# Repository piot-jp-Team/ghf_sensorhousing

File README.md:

# ghf_sensorhousing
## 農園センサーユニットハウジング
- arduino pro mini
- MH-Z19B 二酸化炭素センサ または　S-300G 二酸化炭素センサ
- AM2320 温湿度センサー
- リニア照度センサ
- 土壌水分センサ

## 仕組み
iot通信モジュールへRS485で取得データを送ります。  
sakura.io + arduino UNO  
sakura.ioから、laravel製のグラフで表示します。  
https://github.com/piot-jp-Team/ghf_webapp （日々更新中）  

sakura.ioとの接続（Web Socket部分）は、https://github.com/piot-jp-Team/ghf_sakuraIO_wss_client  
今後はsigfox,lorawanも利用したいと思います。

## 使用するライブラリ   
(サーバ側)
- nginx, php7
- websocket クライアント　ratchetphp/Pawl
- phpフレームワーク laravel 5.6
- LaravelCharts
- mysql 5.7

(組み込み側)
- Arduino
- modbus/master slave
- S-300G or mhz19_uart
- Adafruit_Sensor
- Adafruit_AM2320
- sakura.io

## 開発ツール
- 筐体設計 OpenSCAD, FreeCAD
- PCB設計 Eagle6.6
- ファームウエア arduino IDE1.8.5
- エディタはATOM, PlantUML, Netbeans etc.

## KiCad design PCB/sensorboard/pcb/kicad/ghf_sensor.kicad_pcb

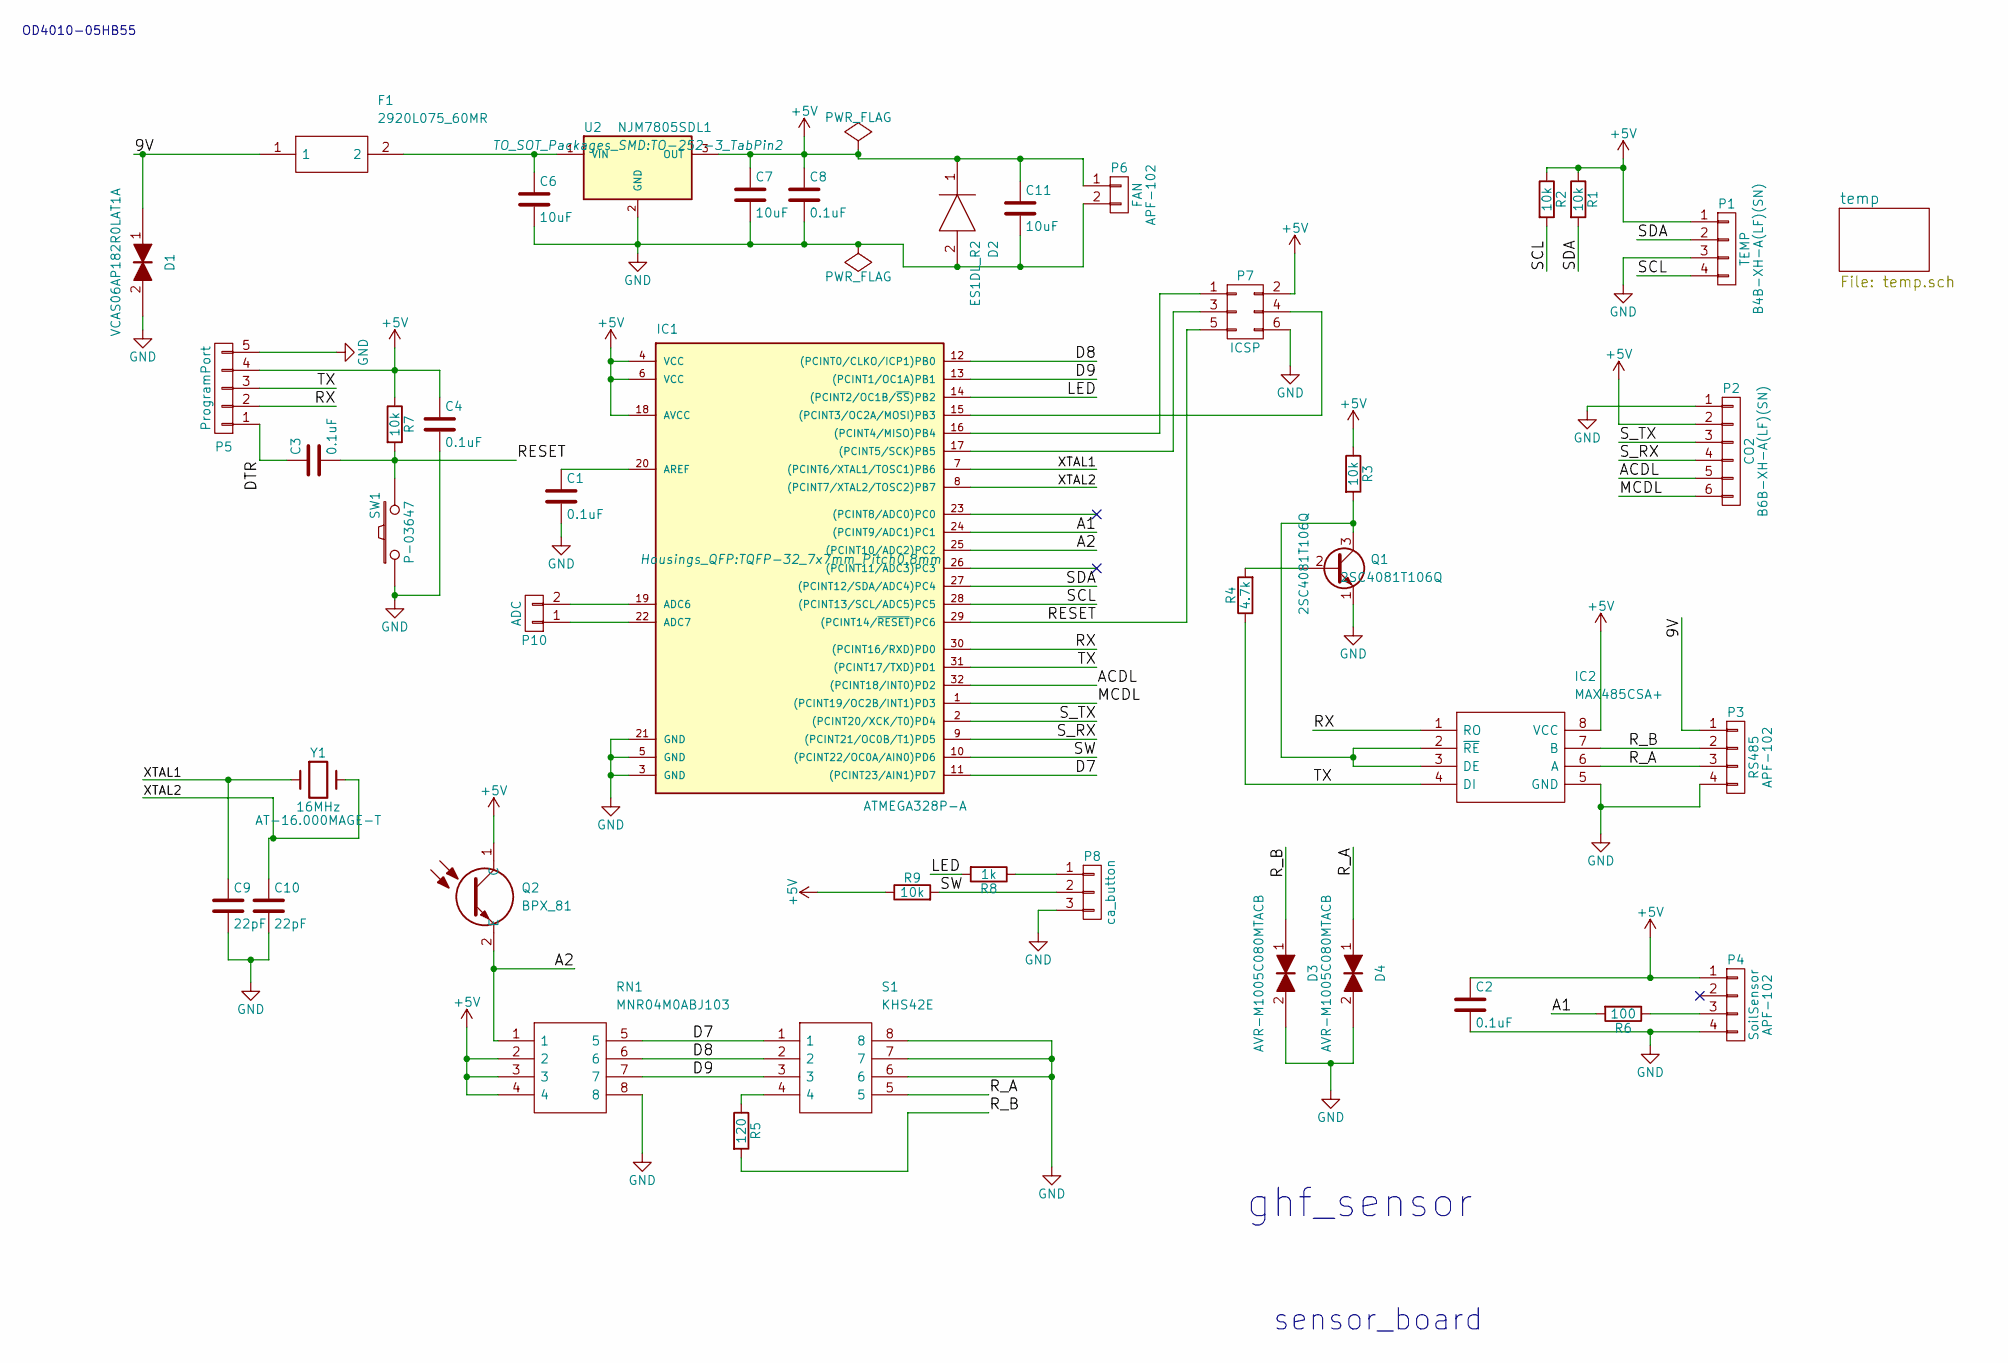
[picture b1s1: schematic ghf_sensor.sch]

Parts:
C1, C2, C3, C4, C8: 0.1uF; C_0603
C6, C7, C11: 10uF; C_0805
C9, C10: 22pF; C_0603
D1: VCAS06AP182R0LAT1A; C_0603
D2: ES1DL_R2; SODFL3618X143N; Mouser Part Number 821-ES1DLR2
D3, D4: AVR-M1005C080MTACB; C_0402
F1: 2920L075_60MR; FUSC7451X180N; Manufacturer_Part_Number 2920L075/60MR; Mouser Part Number 576-2920L075/60MR
IC1: ATMEGA328P-A; TQFP-32_7x7mm_Pitch0.8mm
IC2: MAX485CSA+; SOIC127P600X175-8N; Mouser Part Number 700-MAX485CSA
P1: TEMP; Pin_Header_Straight_1x04_Pitch2.54mm
P2: CO2; Pin_Header_Straight_1x06_Pitch2.54mm
P3: RS485; TerminalBlock_bornier-4_P5.08mm
P4: SoilSensor; TerminalBlock_bornier-4_P5.08mm
P5: ProgramPort; Pin_Header_Straight_1x05_Pitch2.54mm
P6: FAN; TerminalBlock_bornier-2_P5.08mm
P7: ICSP; Pin_Header_Straight_2x03_Pitch2.54mm
P8: ca_button; Pin_Header_Straight_1x03_Pitch2.54mm
P10: ADC; Pin_Header_Straight_1x02_Pitch2.54mm
Q1: 2SC4081T106Q; SOT-323_SC-70
Q2: BPX_81; BPX81; Manufacturer_Part_Number BPX 81; Mouser Part Number 720-BPX81
R1, R2, R3, R7, R9: 10k; R_0603
R4: 4.7k; R_0603
R5: 120; R_0603
R6: 100; R_0603
R8: 1k; R_0603
RN1: MNR04M0ABJ103; RESCAX50P100X200X36-8N; Manufacturer_Part_Number MNR04M0ABJ103
S1: KHS42E; SOIC127P812X230-8N; Manufacturer_Part_Number KHS42E
SW1: P-03647; SW_PUSH_6mm
U2: NJM7805SDL1; TO-252-3_TabPin2
Y1: 16MHz; Crystal_SMD_HC49-SD

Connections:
+5V: C2.1, C4.1, C7.1, C8.1, C11.1, D2.1, IC1.4 (VCC), IC1.6 (VCC), IC1.18 (AVCC), IC2.8 (VCC), P1.1, P2.2, P4.1, P5.4, P6.1, P7.2, Q2.1 (C), R1.1, R2.1, R3.1, R7.1, R9.1, RN1.2, RN1.3, RN1.4, U2.3 (OUT)
/9V: D1.1, F1.1, P3.1
/A1: IC1.24 ((PCINT9/ADC1)PC1), R6.2
/A2: IC1.25 ((PCINT10/ADC2)PC2), Q2.2 (E), RN1.1
/ACDL: IC1.32 ((PCINT18/INT0)PD2), P2.5
/D7: IC1.11 ((PCINT23/AIN1)PD7), RN1.5, S1.1
/D8: IC1.12 ((PCINT0/CLKO/ICP1)PB0), RN1.6, S1.2
/D9: IC1.13 ((PCINT1/OC1A)PB1), RN1.7, S1.3
/DTR: C3.1, P5.1
/LED: IC1.14 ((PCINT2/OC1B/~SS~)PB2), R8.2
/MCDL: IC1.1 ((PCINT19/OC2B/INT1)PD3), P2.6
/RESET: C3.2, IC1.29 ((PCINT14/~RESET~)PC6), P7.5, R7.2, SW1.2
/RX: IC1.30 ((PCINT16/RXD)PD0), IC2.1 (RO), P5.2
/R_A: D4.1, IC2.6 (A), P3.3, S1.5
/R_B: D3.1, IC2.7 (B), P3.2, R5.2
/SCL: IC1.28 ((PCINT13/SCL/ADC5)PC5), P1.4, R2.2
/SDA: IC1.27 ((PCINT12/SDA/ADC4)PC4), P1.2, R1.2
/SW: IC1.10 ((PCINT22/OC0A/AIN0)PD6), P8.2, R9.2
/S_RX: IC1.9 ((PCINT21/OC0B/T1)PD5), P2.4
/S_TX: IC1.2 ((PCINT20/XCK/T0)PD4), P2.3
/TX: IC1.31 ((PCINT17/TXD)PD1), IC2.4 (DI), P5.3, R4.1
/XTAL1: C9.1, IC1.7 ((PCINT6/XTAL1/TOSC1)PB6), Y1.1
/XTAL2: C10.1, IC1.8 ((PCINT7/XTAL2/TOSC2)PB7), Y1.2
GND: C1.2, C2.2, C4.2, C6.2, C7.2, C8.2, C9.2, C10.2, C11.2, D1.2, D2.2, D3.2, D4.2, IC1.3 (GND), IC1.5 (GND), IC1.21 (GND), IC2.5 (GND), P1.3, P2.1, P3.4, P4.4, P5.5, P6.2, P7.6, P8.3, Q1.1 (E), RN1.8, S1.6, S1.7, S1.8, SW1.1, U2.2 (GND)
unnamed: C1.1, IC1.20 (AREF)
unnamed: C6.1, F1.2, U2.1 (VIN)
unnamed: IC1.15 ((PCINT3/OC2A/MOSI)PB3), P7.4
unnamed: IC1.16 ((PCINT4/MISO)PB4), P7.1
unnamed: IC1.17 ((PCINT5/SCK)PB5), P7.3
unnamed: IC1.19 (ADC6), P10.2
unnamed: IC1.22 (ADC7), P10.1
unnamed: IC2.2 (~RE), IC2.3 (DE), Q1.3 (C), R3.2
unnamed: P4.3, R6.1
unnamed: P8.1, R8.1
unnamed: Q1.2 (B), R4.2
unnamed: R5.1, S1.4

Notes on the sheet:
ghf_sensor
sensor_board
OD4010-05HB55

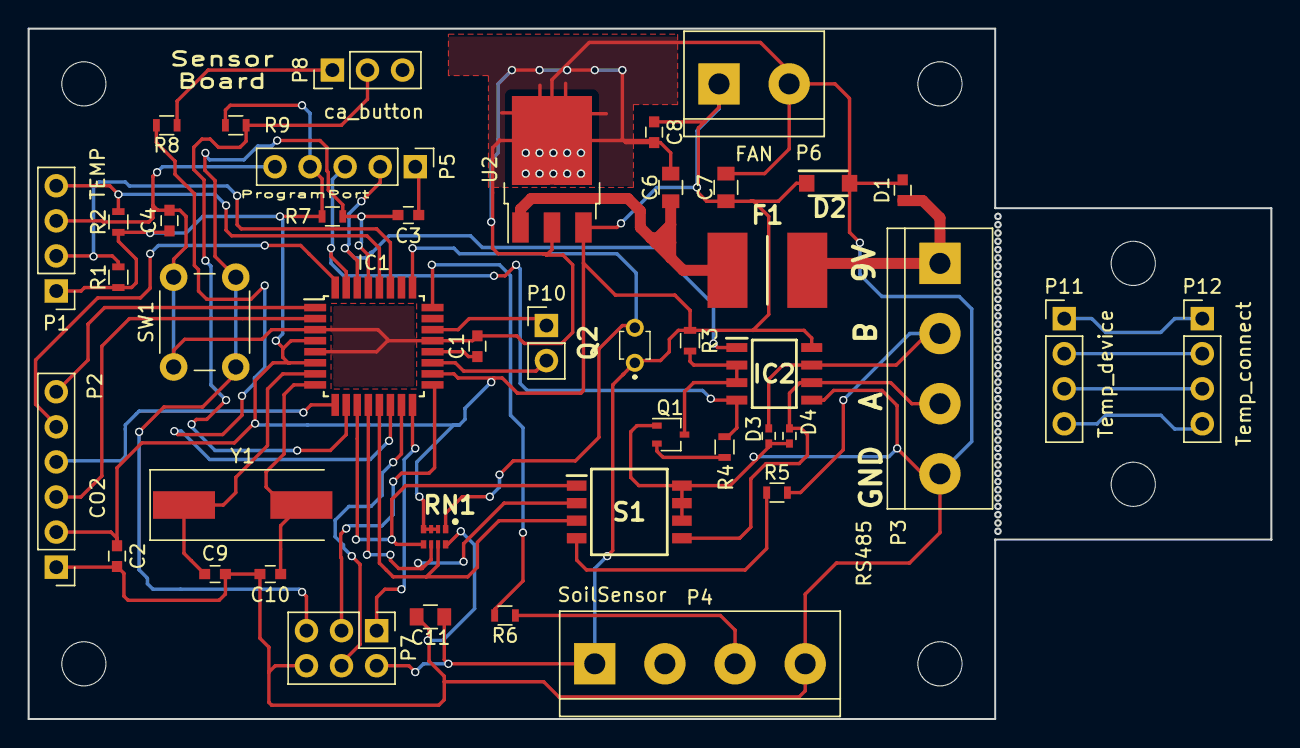
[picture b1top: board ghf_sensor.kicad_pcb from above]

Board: 2 copper layers, 90.0 x 50.0 mm, 44 parts (0 on the bottom side), 40 nets.

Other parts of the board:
P11: Temp_device; Pin_Header_Straight_1x04_Pitch2.54mm
P12: Temp_connect; Pin_Header_Straight_1x04_Pitch2.54mm

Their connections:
unnamed: P11.1, P12.1
unnamed: P11.2, P12.2
unnamed: P11.3, P12.3
unnamed: P11.4, P12.4

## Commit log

2018-03-27 add parts stl
2018-03-28 3D printed mock
2018-03-28 3D modeling
2018-03-28 PCB sensor borad
2018-03-29 PCB modified
2018-05-09 add new file
2018-05-09 modify readme file
2018-05-09 add cad data, modify PCB board and schematic
2018-05-11 add kinoko top cover
2018-05-11 mv stl
2018-05-11 konoko cover modified
2018-05-17 きのこカバー
2018-05-17 add sequence diagram
2018-05-17 readme update
2018-05-17 add firmware
2018-05-17 add sequence diagram2
2018-05-17 secuence diagram Modified
2018-05-17 readme modified
2018-05-21 firmware (ToDo)
2018-05-21 add vacuum forming die
2018-05-21 separate forming die
2018-05-24 read me lib modified
2018-05-29 Add cad covertopkinoko file (iges and FreeCad)
2018-05-29 iges files add
2018-05-29 old iges files remove
2018-05-29 readme
2018-05-30 きのこカバー２Ｄ図面
2018-06-02 ad file ghf_caover_top_kinoko_die.scad
2018-06-02 ad file ghf_caover_top_kinoko_die_sekkou_mold.stl
2018-06-04 ghf_sakura_io
2018-06-04 test
2018-06-05 ghfsensor.ino update
2018-06-06 ghfsensor
2018-06-07 ghf_sakura_io Upd
2018-06-10 samurai test2
2018-06-10 sakura io
2018-06-20 sakura.io arduino holder and antena bracket
2018-06-20 aad rib for screw boss
2018-08-09 servser database ER-diagram
2018-08-10 sakura_io update
2018-10-11 CAD housing update
2018-10-12 sensor firmware s-300g add
2018-10-16 CADD rediation shield add
2018-10-30 CAD Modified
2018-11-19 CAD undercshell modified
2019-02-12 New version ghi_ add
2019-02-13 dimension modified
2019-02-14 bottom screw mounting outer demension modified
2019-02-19 ver201902 update New PCB
2019-02-19 ver201902 old cad data deleted
2019-03-14 modify CAD ghi_pcbstay*
2019-03-19 modify CAD ghi_flowseparater.* 2 hole spacing
2019-04-01 Update README.md
    PCB設計にkicad4.0追加
2019-05-15 calibration sw grommet add
